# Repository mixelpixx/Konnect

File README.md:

<div align="center">

# Konnect has moved to Konnect-EDA

## [Go to Konnect-EDA →](https://github.com/Orchis-ai-LLC/Konnect-EDA)

</div>

This repository is being archived, which makes it read-only. Development continues
at Konnect-EDA, from Orchis.ai LLC.

## It stays free, unless you're a business

Konnect-EDA is now commercial and closed source. Here's what that means for you:

- **Everyone, businesses included:** free until version 1.0.
- **Personal, hobby, student and open-hardware work:** still free after 1.0. You'll
  need a license key, and that key is free too.
- **Businesses:** a paid license from 1.0.

Business licenses pay for the work, and that's what lets us keep it free for
everyone else.

**Nothing here is being taken away.** The code and releases in this repository stay
available under the AGPL-3.0. The original
[KiCAD MCP Server](https://github.com/mixelpixx/KiCAD-MCP-Server) stays open source
under the MIT license and is still maintained. The boards you design are always yours.

## Where to go now

- **Downloads:** the [Konnect-EDA releases page](https://github.com/Orchis-ai-LLC/Konnect-EDA/releases).
  The first release is coming soon.
- **Bugs and feature requests:** the
  [Konnect-EDA issue tracker](https://github.com/Orchis-ai-LLC/Konnect-EDA/issues).
- **Want to help build it?** [Sign up to contribute](https://orchis.ai/konnect/join).
- **Contributed to Konnect?** Please [complete your sign-off](https://orchis.ai/konnect/sign-off)
  by November 20.
- **Using it at a company?** See [licensing](https://konnect-eda.orchis.ai/licensing/).

Thank you to everyone who built Konnect with us.

---

**AI-assisted PCB design for KiCAD 10.** Konnect is a native KiCAD plugin — a single
Rust binary — that lets Claude and other AI assistants design schematics and PCBs
through the [Model Context Protocol](https://modelcontextprotocol.io) (MCP).

**228 tools across 21 on-demand toolsets.** Schematic capture, PCB layout and
routing, ERC/DRC, design-review audits, JLCPCB part search, reference
circuits, and a full manufacturing export pipeline — with bundled skills and agents
that teach Claude KiCAD conventions out of the box.

## Why Konnect exists

Konnect is the successor to [KiCAD-MCP-Server](https://github.com/mixelpixx/KiCAD-MCP-Server),
a Python/TypeScript project that proved AI-driven PCB design works — and, in the
process, showed exactly where that architecture runs out of road. Konnect was built
to fix those specific problems:

**The call path was too long.** In the original server, a single tool call travels
through TypeScript, schema validation, a spawned Python subprocess, JSON over
stdin/stdout, a command router, and finally SWIG-generated C++ proxy objects before
anything touches your board. That's four language and serialization boundaries, each
with its own failure modes — subprocess lifecycle management, stdout parsing that
filters out warnings KiCAD leaks into the stream, chunked-JSON reassembly. In
Konnect, a tool call is a function call. One process, one language, no plumbing.

**The dependency surface was enormous.** Running the original means carrying Node.js
and its npm tree, Python and its pip packages, wxPython, kicad-skip, and KiCAD's
SWIG bindings — two package ecosystems plus a binding layer, every one of them a
moving target that can break an install. Konnect is a single static binary —
20–25 MB depending on platform, a ~9 MB download. There is nothing to install
alongside it and nothing to version-match.

**SWIG is a dead end.** The original's PCB backend depends on KiCAD's SWIG Python
bindings, which KiCAD is deprecating in favor of its IPC API. SWIG also carried
real operational scars: a zone-fill call that can segfault the backend, proxy-object
comparison bugs, and a fallback path that can silently swap backends mid-session.
Konnect talks to KiCAD 10 through the official IPC API (protobuf over NNG) — the
interface KiCAD is investing in — with real-time board edits that integrate with
KiCAD's own undo/redo.

**Schematic edits should not corrupt files.** Konnect edits `.kicad_sch` files
through its own S-expression engine with atomic writes (write, fsync, rename), UUID
preservation, and round-trip tests — no third-party schematic library with known
gaps, no text-manipulation workarounds.

**Context economy is a feature.** Exposing all 228 tools to an LLM costs roughly 23K
tokens of context on every listing. Konnect's router loads a starter kit (~2K
tokens) and lets the model pull in toolsets on demand — plus built-in observability
(`get_recent_calls`, `server_stats`, JSONL call logs) so the model can diagnose its
own tool failures.

The result is smaller, faster to install, aligned with where KiCAD is going, and
built for production use rather than experimentation. The original project remains
open, maintained, and useful — see [the comparison below](#relationship-to-kicad-mcp-server).

## What it does

Instead of describing changes and applying them by hand, the AI works your project
directly:

- **Place and wire schematic components** — add resistors, ICs, connectors; wire them
  together by pin name
- **Lay out the PCB** — place, move, rotate, and route footprints in real time via
  KiCAD's IPC API, with full undo/redo integration
- **Run design checks** — ERC, DRC, connectivity validation, decoupling audits,
  power-rail review, BOM health checks
- **Export production files** — Gerbers, drill, BOM, pick-and-place, 3D models, PDF
- **Search JLCPCB parts** — find in-stock components in a local 2.5M-part catalog and
  suggest alternatives
- **Start from reference circuits** — USB-C, LDO, buck converter, STM32, I2C, LED
  templates with verified component values
- **Watch it happen** — a live schematic viewer auto-refreshes as the AI edits

The full tool catalog is documented in [tool-directory.md](tool-directory.md).

## How it works

| Layer | Mechanism |
|-------|-----------|
| Schematic editing | Direct `.kicad_sch` S-expression editing with atomic writes (no KiCAD required) |
| PCB editing | KiCad 10 IPC API (NNG + protobuf) — real-time and undo-aware; single-footprint placement has a safe headless fallback |
| Specctra routing | Revision-bound Rust DSN export, local Freerouting MCP routing, and strict one-transaction SES import; an authenticated KiCad 10 native-export bridge is explicit opt-in |
| Exports & checks | `kicad-cli` subprocess (Gerber, PDF, ERC, DRC, …) |
| Transport | MCP JSON-RPC over stdio (default), or Streamable HTTP (`transport = "http"` / `"both"`) |

Explore the request path and safety boundaries in the
[interactive architecture diagrams](docs/ARCHITECTURE_DIAGRAMS.md). They are
published from a standalone documentation repository and add no dependencies to
Konnect.

## Installation

### From the KiCAD Plugin Manager (recommended)

1. Download the package for your OS from [Releases](https://github.com/mixelpixx/Konnect/releases):
   `konnect-pcm-v<version>-windows.zip`, `-macos.zip`, or `-linux.zip`. Each
   bundles that platform's server binary — the macOS package is a universal
   build, so one download covers Apple Silicon and Intel. (The `konnect-pcm-*`
   assets are the KiCAD plugin packages; the other archives are standalone
   server binaries.)
2. Open KiCAD 10 → **Plugin and Content Manager**
3. Click **Install from File** and select the zip
4. Restart KiCAD

Verify: open the **PCB Editor** → **Tools → External Plugins** → you should see
**Konnect**.

For KiCad 10, the Konnect settings dialog also offers an optional **native
Specctra bridge**. When enabled, `export_specctra_dsn` can ask the active PCB
Editor to generate its native DSN while Konnect still binds the export to the
exact IPC snapshot and creates the strict reverse manifest used during SES
import. The bridge is local-only, authenticated, disabled by default, and not
the KiCad 11 integration path. Konnect uses its Rust exporter by default;
`native_bridge_mode: "prefer"` enables fallback to Rust when the bridge is
unavailable, while `"require"` refuses instead.

For end-to-end autorouting, run `check_freerouting`, then
`export_specctra_dsn` → `route_specctra_dsn` →
`plan_specctra_ses_import` / `apply_specctra_ses`. Readiness reports engine
discovery, native-MCP compatibility, and complete bridge availability
separately. The owned Java child is loopback-only and is reaped on success,
failure, timeout, or cancellation. The first supported profile preserves fixed
straight tracks and through vias; unlocked routing, arcs, zones, and unsupported
geometry are rejected before mutation.

### Build from source

```bash
# protoc is required (protobuf code generation), and cmake (the nng crate
# compiles the NNG C library with it).
# Windows: choco install protoc cmake
# macOS:   brew install protobuf cmake
# Linux:   apt install protobuf-compiler cmake
cargo build --release -p konnect
```

### Install guidance for your AI client

Konnect bundles shared KiCad skills for Claude and Codex. Select the client when
installing, checking, or removing that guidance:

```bash
# Existing behavior remains the default: Claude skills, agents, and hooks
konnect init

# Codex installs only the shared skills under ~/.agents/skills
konnect init --client codex
konnect status --client codex
konnect uninstall --client codex
```

MCP server startup never installs or restores guidance. Run `konnect init`
explicitly when you want those files installed; after `konnect uninstall`,
starting the server leaves them removed.

Guidance written by an older `konnect init` is not updated by upgrading the
binary. `konnect status` compares every installed skill, agent, and hook with
the bundle in the binary you run and marks each `current`, `different`, or
`missing`. The server makes the same check once for each installed version:
the first start after `konnect init` compares the files, records
the result in `~/.konnect`, and adds a one-line notice to its `initialize`
instructions if guidance is out of sync. Later starts reuse that record, so
guidance you chose to keep is not reported again. `get_installation_info`
shows the result. Re-run `konnect init` to update it.
It overwrites differing files, so keep a copy of any file you edited. `--client` remains accepted in server
commands for compatibility. For example, register a standalone binary with the
Codex CLI using:

```bash
codex mcp add konnect -- /path/to/konnect --client codex
```

Claude remains the default when `--client` is omitted. The installer tracks the
two clients independently, and a Codex install does not create or modify
`~/.claude`.

`--help` on any subcommand prints that subcommand's usage and writes nothing —
`konnect init --help` describes the installer rather than running it. An
argument Konnect does not recognise is an error rather than being ignored, so a
typo such as `--cleint codex` stops instead of quietly installing for the
default client.

To verify which Konnect process an MCP client is actually using, call the
always-visible `get_installation_info` tool. It reports the serving build,
executable path, verified installation source when one can be proven, KiCad
CLI and IPC detection, and restart guidance. A missing build commit or an
`unknown` installation source means the available evidence was insufficient;
it is not silently guessed from a directory name.

### macOS

The [Releases](https://github.com/mixelpixx/Konnect/releases) page ships
standalone server binaries for both Apple Silicon (`aarch64-apple-darwin`) and
Intel (`x86_64-apple-darwin`). They are not yet code-signed, so if you download
one through a browser, clear the quarantine flag before first launch:

```bash
tar xzf konnect-v*-aarch64-apple-darwin.tar.gz
xattr -d com.apple.quarantine ./konnect   # only needed for browser downloads
./konnect --help
```

Or build from source as above (verified on Apple Silicon; the same
`target/release/konnect` binary is the MCP server).

KiCad on macOS keeps its tools inside the app bundle and they are not on
`PATH`, so point Konnect at them in `~/Library/Application Support/konnect/config.toml`:

```toml
kicad_cli = "/Applications/KiCad/KiCad.app/Contents/MacOS/kicad-cli"
kicad_binary = "/Applications/KiCad/KiCad.app/Contents/MacOS/kicad"
# KiCad 10's IPC socket on macOS (enable it in KiCad:
# Preferences → Plugins → "Enable KiCad API")
ipc_address = "ipc:///tmp/kicad/api.sock"
```

Claude Desktop's config lives at
`~/Library/Application Support/Claude/claude_desktop_config.json`:

```json
{
  "mcpServers": {
    "konnect": {
      "command": "/path/to/konnect"
    }
  }
}
```

For Claude Code, put the same snippet in a `.mcp.json` in your project root.

The macOS PCM package (`konnect-pcm-v<version>-macos.zip`) bundles a universal
server binary, so one download covers Apple Silicon and Intel. The schematic
viewer compiles and launches on macOS (Tauri 2 uses the system WKWebView —
WebView2 is only a Windows requirement) but hasn't had the same mileage as
the Windows build yet.

## Setup with Claude Desktop

After a PCM install, the server binary lives in your KiCAD documents folder:

```
C:\Users\<YOU>\Documents\KiCad\10.0\3rdparty\plugins\com_github_mixelpixx_konnect\bin\konnect.exe
```

Edit `%APPDATA%\Claude\claude_desktop_config.json`:

```json
{
  "mcpServers": {
    "konnect": {
      "command": "C:\\Users\\<YOU>\\Documents\\KiCad\\10.0\\3rdparty\\plugins\\com_github_mixelpixx_konnect\\bin\\konnect.exe"
    }
  }
}
```

Restart Claude Desktop and the Konnect tools appear. For Claude Code, drop the same
snippet into a `.mcp.json` in your project root (see [examples/](examples/)).

## Schematic viewer

A standalone viewer that auto-refreshes as the schematic file changes:

```bash
schematic-viewer.exe path\to\your\root_schematic.kicad_sch
```

Point it at the root sheet of a hierarchical design and every sub-sheet is rendered
too, with a depth-indented sheet selector in the toolbar. Edits saved from KiCAD (or
made by the AI through the schematic tools) re-render only the sheets that changed
and refresh the view live — rendering runs against temp-folder snapshots, so the
viewer never blocks KiCAD from saving. Pan with click-drag, zoom with the wheel,
`0` to fit, `R` to refresh, drag-and-drop to open a different file. Also launchable
by the AI via the `open_schematic_viewer` tool.

Needs the WebView2 runtime (pre-installed on Windows 10/11) and a KiCAD install for
`kicad-cli` (auto-discovered, or pass `--kicad-cli <path>`). Built separately from
the main workspace — see [DEV.md](DEV.md) for build steps.

## Requirements

- KiCAD 10 (Windows is the most-tested platform; macOS works from the release
  binaries or a source build — see the [macOS section](#macos) above. Linux
  compiles and passes tests in CI but hasn't had per-platform QA yet; both are
  tracked on the [roadmap](ROADMAP.md))
- `kicad-cli` (ships with KiCAD — used for exports, ERC, DRC)
- For most PCB tools: KiCAD running with the target board open (IPC API).
  `place_component`, `move_component`, `rotate_component`, and (on KiCAD
  10.0.6+) `flip_component` can safely fall back to a closed board file when
  IPC is unreachable. An older reachable KiCAD makes `flip_component` fail
  closed with `unsupported_capability`; it never edits the file underneath a
  live editor that cannot perform the native flip.

## License: free for the little guys

Konnect is licensed under the **[GNU AGPL-3.0](LICENSE)**.

If you're a hobbyist, student, freelancer, or open-source project: **use it freely,
no strings attached.** Design boards, ship them, sell them.

If you're a business: the AGPL requires that anything you build on or around Konnect —
including software provided over a network — be open-sourced under the same license.
If that doesn't work for you, **commercial licenses are available**: see
[COMMERCIAL.md](COMMERCIAL.md).

## Relationship to KiCAD-MCP-Server

The original [Python/TypeScript project](https://github.com/mixelpixx/KiCAD-MCP-Server)
remains fully open (MIT) and maintained. Konnect is where new development happens —
the architecture it proved, rebuilt for production:

| | KiCAD-MCP-Server | Konnect |
|---|---|---|
| Runtime | Node.js + Python + SWIG bindings | Single static binary (20–25 MB) |
| Tool call path | TS → subprocess → Python → SWIG C++ | Direct function call |
| PCB backend | SWIG (deprecated by KiCAD) + experimental IPC | KiCAD 10 IPC API |
| Schematic backend | kicad-skip + custom loaders | Native S-expression engine, atomic writes |
| Context cost | Router pattern | Load/unload toolsets + observability |
| Skills / agents | — | 6 skills + 2 agents bundled |
| License | MIT | AGPL-3.0 + commercial |

## Troubleshooting

**Plugin doesn't appear in KiCAD** — install via the Plugin and Content Manager (not
manual copy), then restart KiCAD.

**PCB tools return "KiCAD must be running with the board loaded"** — open KiCAD
with that board first; most PCB tools talk to the running PCB editor. Only an
unreachable KiCAD produces that message: if KiCAD is running and the tool
refuses anyway, the error is the tool's own reason for refusing.
`place_component`, `move_component`, `rotate_component`, and (on KiCAD
10.0.6+) `flip_component` can fall back to a closed board file when no KiCAD
process is reachable. An older, reachable KiCAD makes `flip_component` refuse
rather than silently editing the file underneath it.

See [docs/TROUBLESHOOTING.md](docs/TROUBLESHOOTING.md) for socket setup, tools
that don't appear after `load_toolset`, and transaction recovery.

**"kicad-cli not found"** — common install paths are auto-detected; set the path
explicitly in the plugin settings dialog, in a `settings.json` beside the binary,
or in a `konnect.toml` in the working directory. (A file under any other name
works only when passed with `--config`.)

## Support

- Community Discord: [join the Konnect community](https://discord.gg/NVp9RGMmDu)
  for installation help, AI-client setup, design-workflow discussion,
  contributor coordination, and live project-status updates
- Issues & feature requests: [GitHub Issues](https://github.com/mixelpixx/Konnect/issues)
- Roadmap: [ROADMAP.md](ROADMAP.md)
- Contributing: [CONTRIBUTING.md](CONTRIBUTING.md)

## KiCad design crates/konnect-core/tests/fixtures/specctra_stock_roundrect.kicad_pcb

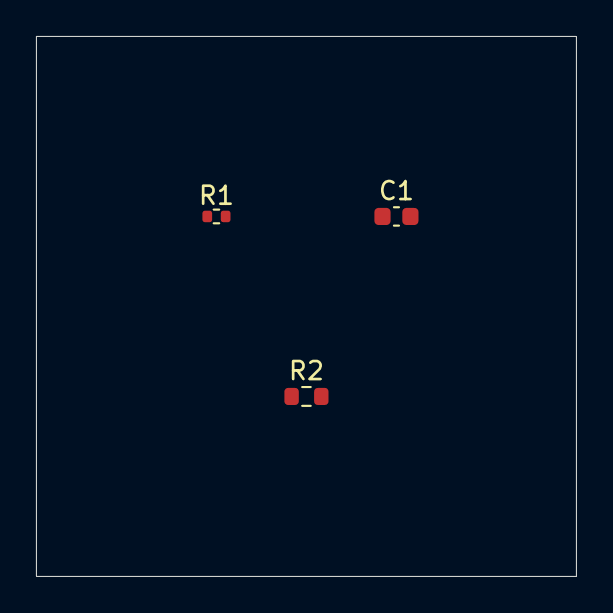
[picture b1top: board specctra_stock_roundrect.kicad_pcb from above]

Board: 2 copper layers, 30.0 x 30.0 mm, 3 parts (0 on the bottom side), 3 nets, no tracks yet.

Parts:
C1: C_0603_1608Metric
R1: R_0402_1005Metric
R2: R_0603_1608Metric

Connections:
GND: C1.2, R2.2
SIG: C1.1, R1.2
VCC: R1.1, R2.1

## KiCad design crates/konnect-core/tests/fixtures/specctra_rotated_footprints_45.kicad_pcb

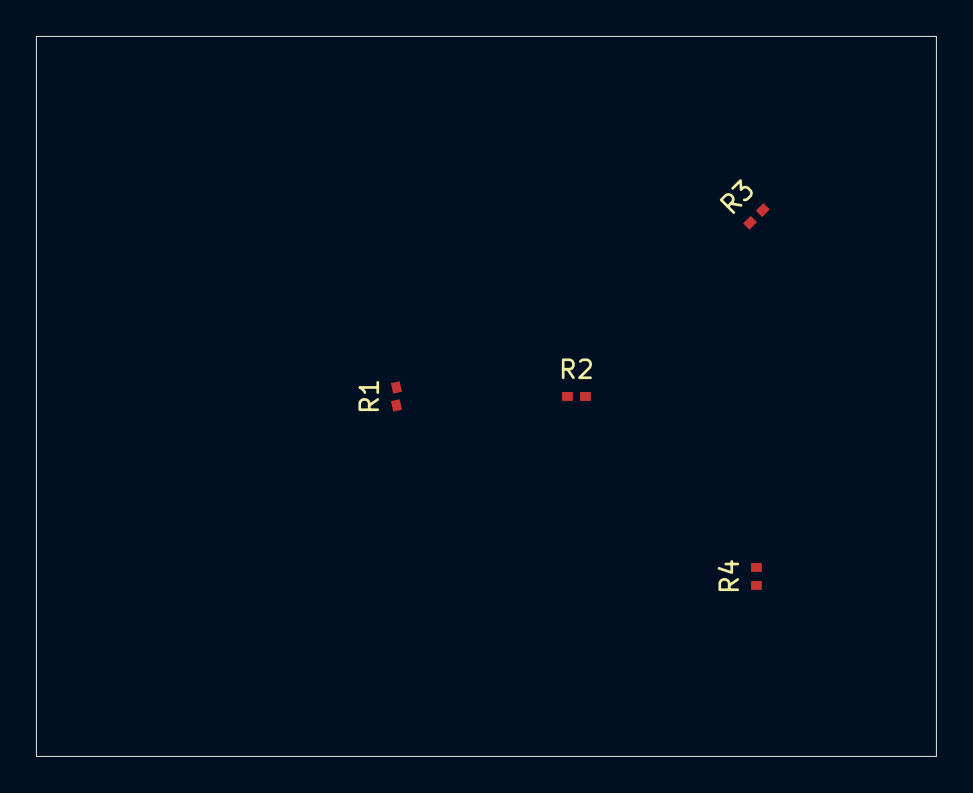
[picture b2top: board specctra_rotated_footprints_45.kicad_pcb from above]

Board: 2 copper layers, 50.0 x 40.0 mm, 4 parts (0 on the bottom side), 2 nets, no tracks yet.

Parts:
R1: 10k; R_0402
R2, R3, R4: 4.7k; R_0402

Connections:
GND: R1.2, R2.1, R3.2, R4.1
VCC: R1.1, R2.2, R3.1, R4.2
